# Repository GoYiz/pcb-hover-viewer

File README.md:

# PCB Hover Viewer

在线查看手机主板并进行“hover 关系高亮”的 Web 应用。

## 技术栈
- Next.js（App Router）
- TypeScript
- SQLite3 + Prisma
- Zustand
- （可选）PixiJS

## 核心能力（当前实现）
- 板卡列表/元信息 API
- 元件与走线几何 API
- 关系查询 API（component -> direct/net/trace）
- 板卡查看页 `/board/[id]`
- **互联网默认示例页 `/examples`（Python 抓取并预处理）**
- Hover 元件联动高亮：
  - 目标元件高亮
  - 直接关联元件高亮
  - 关联 Trace 高亮
- 关系侧边栏信息展示

## 快速开始
```bash
npm install
npm run db:generate
npm run db:push
npm run db:seed
npm run dev
```

打开：`http://localhost:3000/board/iphone-mainboard-demo`

## 目录结构
```text
app/
  api/boards/...        # API 路由
  board/[id]/page.tsx   # 查看器页面
components/
  BoardViewerClient.tsx
  PcbCanvas.tsx
lib/
  prisma.ts
  api.ts
prisma/
  schema.prisma
  seed.ts
store/
  viewerStore.ts
types/
  pcb.ts
```

## 架构文档
- `docs/ARCHITECTURE.md`

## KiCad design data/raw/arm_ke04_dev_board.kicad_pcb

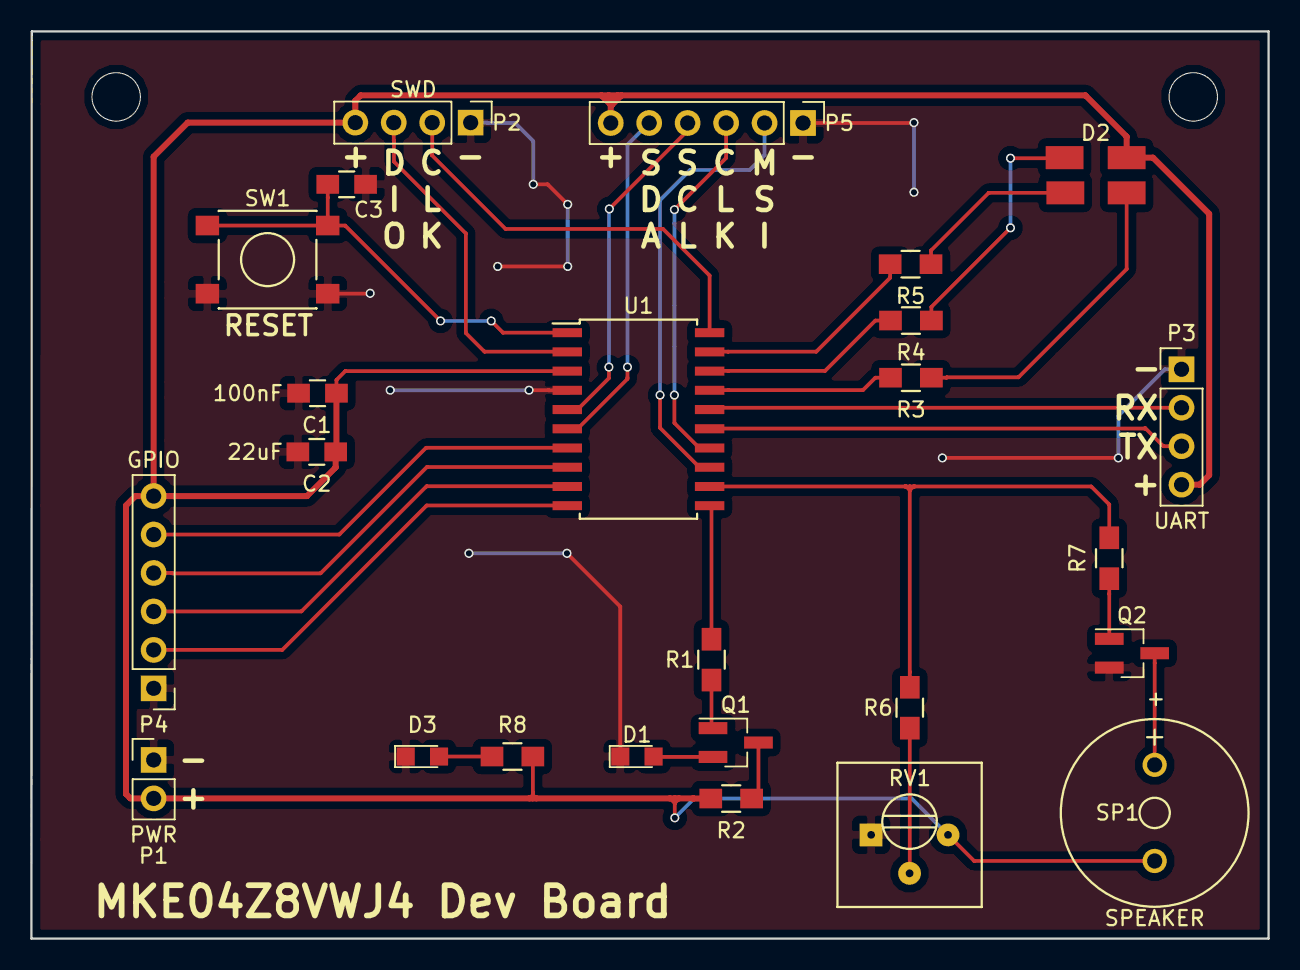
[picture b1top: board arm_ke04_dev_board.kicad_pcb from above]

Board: 2 copper layers, 81.7 x 59.9 mm, 25 parts (0 on the bottom side), 30 nets.

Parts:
C1, C3: 100nF; C_0805_HandSoldering
C2: 22uF; C_0805_HandSoldering
D1, D3: LED; LED_0805
D2: Led_RGB_CA; 4PLED+
P1: PWR; Pin_Header_Straight_1x02_Pitch2.54mm
P2: SWD; Pin_Header_Straight_1x04_Pitch2.54mm
P3: UART; Pin_Header_Straight_1x04_Pitch2.54mm
P4: GPIO; Pin_Header_Straight_1x06_Pitch2.54mm
P5: SPECIAL; Pin_Header_Straight_1x06_Pitch2.54mm
Q1: Q_NPN_BCE; SOT-23_Handsoldering
Q2: Q_NMOS_GSD; SOT-23_Handsoldering
R1: 10K; R_0805_HandSoldering
R2: 500R; R_0805_HandSoldering
R3, R4, R5, R8: 1K; R_0805_HandSoldering
R6, R7: 0R; R_0805_HandSoldering
RV1: POT; Potentiometer_Trimmer-Suntan-TSR-3386P
SP1: SPEAKER; MagneticBuzzer_ProSignal_ABT-410-RC
SW1: SW_PUSH_SMALL; SW_SPST_PTS645
U1: MKE04Z8VWJ4; SOIC-20W_7.5x12.8mm_Pitch1.27mm

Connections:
/I2C_SCL: P5.4, U1.5
/I2C_SDA: P5.5, U1.6
/RESET: C3.1, SW1.1, U1.1
/SPI_CLK: P5.3, U1.14
/SPI_MOSI: P5.2, U1.13
/SWD_CLK: P2.2, U1.20
/SWD_DIO: P2.3, U1.2
/UART_RX: P3.2, U1.16
/UART_TX: P3.3, U1.15
GND: C1.2, C2.2, C3.2, D1.1, D3.1, P1.1, P2.1, P3.1, P4.1, P5.1, Q2.2, RV1.1, SW1.2, U1.4
unnamed: D1.2, Q1.2
unnamed: D2.2, R3.1
unnamed: D2.3, R4.1
unnamed: D2.4, R5.1
unnamed: D3.2, R8.1
unnamed: P4.2, U1.10
unnamed: P4.3, U1.9
unnamed: P4.4, U1.8
unnamed: P4.5, U1.7
unnamed: Q1.1, R1.1
unnamed: Q1.3, R2.1
unnamed: Q2.1, R7.1
unnamed: Q2.3, SP1.2
unnamed: R1.2, U1.11
unnamed: R3.2, U1.17
unnamed: R4.2, U1.18
unnamed: R5.2, U1.19
unnamed: R6.1, RV1.2
unnamed: R6.2, R7.2, U1.12
VDD: C1.1, C2.1, D2.1, P1.2, P2.4, P3.4, P4.6, P5.6, R2.2, R8.2, RV1.3, SP1.1, U1.3

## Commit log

2026-04-07 docs: add architecture design for pcb hover viewer
2026-04-07 docs: switch architecture to nextjs + sqlite with optional python pipeline
2026-04-07 feat: implement nextjs sqlite pcb hover viewer mvp
2026-04-07 fix: align react version with next 15 peer deps
2026-04-07 build: run prisma generate before next build
2026-04-07 chore: upgrade next to 15.5.6 for security patch
2026-04-07 chore: upgrade next to 16.2.2
2026-04-07 feat: add internet-sourced default examples with python preprocessing
2026-04-07 fix: parse traces and enable hover reactions for both components and traces
2026-04-07 feat: add animated trace flow and target pulse effects
2026-04-07 feat: replace svg mvp renderer with pixijs high-performance canvas renderer
2026-04-07 feat: restore trace flow and add layered pixi rendering with partial redraw
2026-04-07 feat: add zoom pan lod and relation request throttling cache
2026-04-07 feat: add box zoom minimap and client-side zero-request relation index
2026-04-07 feat: add layer toggles and component search-focus with box zoom and minimap refinements
2026-04-07 fix: restore highlight effect and finalize layer toggle plus component search focus
2026-04-07 fix: make visibleLayers prop optional for backward compatibility
2026-04-07 feat: add unified 2d/3d view mode with threejs renderer and shared interaction state
2026-04-07 fix: add @types/three and update typedRoutes config
2026-04-07 feat: apply unified tscircuit-inspired workbench ui and shared 2d-3d visual language
2026-04-08 fix: restore full workbench ui implementation after style redesign
2026-04-12 fix: restore renamed board api helpers for workbench ui
2026-04-12 fix: accept legacy board props in workbench client component
2026-04-12 feat: add leafer 2d validation renderer alongside pixi and three
2026-04-12 feat: add zoom pan box-zoom and focus navigation to leafer validation renderer
2026-04-12 fix: guard leafer rect position and size values for type safety
2026-04-12 refactor: switch default 2d renderer from pixi to leafer globally
2026-04-12 fix: dynamically import leafer-based 2d canvas to avoid server prerender issues
2026-04-12 fix: disable ssr for leafer-dependent board and examples pages
2026-04-12 fix: restore standard page wrappers after invalid dynamic server component attempt
2026-04-12 fix: force dynamic rendering for leafer-dependent pages
2026-04-12 fix: serve demo board page from built-in data to isolate leafer runtime issue
2026-04-12 debug: replace leafer workbench canvas with minimal runtime probe
2026-04-12 fix: restore dynamic canvas imports in workbench after debug probe
2026-04-12 debug: switch leafer probe to official nextjs init pattern
2026-04-12 fix: relax leafer probe local typing to match runtime api
2026-04-12 feat: restore real pcb primitives rendering with official leafer init
2026-04-12 feat: restore hover and relation highlight in leafer renderer
2026-04-12 feat: restore zoom pan and box-zoom interactions in leafer renderer
2026-04-12 perf: cache leafer nodes and switch hover updates to partial redraw
2026-04-12 feat: add grid crosshair and layer hud to leafer workbench
2026-04-12 feat: add selection and box-select interactions to leafer workbench
2026-04-12 feat: add measurement tool and update leafer interaction tips
2026-04-12 feat: add measurement tool to leafer workbench
2026-04-12 feat: enhance measurement tool with preview esc clear and delta display
2026-04-12 feat: add point snapping to leafer measurement tool
2026-04-12 feat: add orthogonal constraint and snap highlight to measurement tool
2026-04-12 feat: persist multiple measurements in leafer workbench
2026-04-12 feat: add measurement list panel to leafer workbench
2026-04-12 feat: add selectable measurement rows and per-item delete
2026-04-12 feat: add clear copy and hover interactions to measurement panel
2026-04-12 feat: add append selection and append box select interactions
2026-04-12 feat: add subtract box select and selection status bar
2026-04-12 feat: add selected objects panel to leafer workbench
2026-04-12 feat: add center and zoom actions for selected objects
2026-04-12 feat: add projection guides to measurement tool
2026-04-12 feat: add copy all measurements action
2026-04-12 fix: repair copy all measurements newline handling
2026-04-12 feat: add top and side toolbars to leafer workbench
2026-04-12 feat: add keyboard help overlay to leafer workbench
2026-04-12 feat: add inspector panel to leafer workbench
2026-04-12 feat: persist viewer url state for camera selection and layers
2026-04-12 test: add canvas state bridge for url state verification
2026-04-12 test: add synthetic 4x4 stress board example for performance validation
2026-04-12 feat: enhance search with focus select and zoom actions
2026-04-12 feat: add export actions for workbench shot and text
2026-04-12 fix: derive export filenames from current path
2026-04-12 feat: add measurement csv and selection json exports
2026-04-12 feat: add selection filter modes for components and traces
2026-04-12 feat: add fine-grained detail visibility toggles in leafer view
2026-04-12 feat: add adaptive label density strategy for leafer view
2026-04-12 fix: type adaptive label visibility state explicitly
2026-04-12 feat: add major and minor adaptive grid rendering
2026-04-12 feat: make trace hit radius adaptive to width and zoom
2026-04-12 feat: enhance relation inspector summaries for hover and multi-select
2026-04-12 feat: enhance measurement snapping with segment projection and center priority
2026-04-12 fix: write selection to url when focusing search result
2026-04-12 feat: persist tool filter and detail visibility in viewer url
2026-04-12 fix: type url-restored tool and filter states explicitly
2026-04-13 test: expose selection filter in canvas state bridge
2026-04-13 feat: export unified workbench session json
2026-04-13 feat: redesign pcb viewer with industrial console aesthetic
2026-04-13 feat: polish console ui with summary rail and richer inspector hierarchy
2026-04-13 feat: surface live canvas state in console summary rail
2026-04-13 feat: polish examples catalog with summary rail and dossier layout
2026-04-14 style: refine typography and spacing across console ui
2026-04-14 style: add restrained motion polish to console surfaces
2026-04-14 test: expose last export action in canvas state bridge
2026-04-14 test: add dom trigger for session export verification
2026-04-14 chore: remove temporary session export dom trigger
2026-04-14 fix: repair bridge text parsing for live summary rail
2026-04-14 feat: share selection and focus state across 2d and 3d views
2026-04-14 fix: pass shared selection props only to 3d canvas
2026-04-14 feat: extend shared 2d 3d state with view mode and clear selection
2026-04-14 feat: preserve relation target semantics from shared selection
2026-04-16 feat: add first-pass IPC-2581 importer and sample fixture
2026-04-16 feat: add first-pass ODB++ importer and sample fixture
2026-04-16 feat: improve importer bbox and net binding heuristics
2026-04-16 feat: expand importer geometry coverage for ipc and odb
2026-04-16 feat: improve ipc geometry extraction from layer features
2026-04-16 feat: complete ipc geometry importer with profile and hole support
2026-04-16 feat: harden ipc importer for production use
2026-04-16 feat: surface import telemetry in viewer ui
2026-04-16 feat: ship ipc import metadata artifacts
2026-04-16 fix: correct ipc component placement and net extraction
2026-04-16 feat: add ipc semantic trace classification
2026-04-16 docs: record ipc semantic alignment baseline
2026-04-17 feat: refine ipc geometry buckets and telemetry
2026-04-17 fix: remove duplicate geometry bucket declaration
2026-04-17 fix: sync import metadata geometry count types
2026-04-17 refactor: declutter ipc telemetry panels
2026-04-17 feat: render ipc pads and keepouts in 2d viewer
2026-04-17 feat: render ipc silkscreen overlay in 2d viewer
2026-04-17 feat: render ipc drill overlay in 2d viewer
2026-04-17 feat: add 2d overlay visibility controls
2026-04-17 feat: render ipc zones in 2d viewer
2026-04-17 feat: render ipc vias in 2d viewer
2026-04-17 refactor: organize 2d overlay controls
2026-04-17 feat: sync live overlay visibility into examples panel
2026-04-17 feat: add overlay visibility presets
2026-04-17 feat: highlight active overlay presets
2026-04-17 feat: bring overlay system into main board viewer
2026-04-17 refactor: surface live overlays in main board viewer
2026-04-17 feat: extend board geometry api contract for overlays
2026-04-17 feat: split board overlays into dedicated geometry model
2026-04-17 fix: add demo fallbacks for hosted board APIs
2026-04-17 feat: unify hosted board fallbacks for examples
2026-04-17 feat: render non-copper overlay geometry buckets
2026-04-18 feat: polish viewer overlay families and initial buckets
2026-04-18 feat: add viewer overlay family controls
2026-04-18 feat: sync overlay telemetry and add legends
2026-04-18 fix: refresh canvas bridge after overlay preset sync
2026-04-18 feat: align three viewer with overlay families
2026-04-18 feat: add three viewer state bridge and overlay materials
2026-04-18 feat: polish three viewer legend and overlay materials
2026-04-18 feat: add overlay inspect support for three viewer
2026-04-18 feat: add overlay inspect and family bucket summaries
2026-04-18 fix: restore three overlay hover registration
2026-04-18 feat: add accessible overlay inspect targets
2026-04-18 feat: add qa panel and example overlay targets
2026-04-18 feat: add viewer debug regression coverage
2026-04-18 feat: add inspect-aware viewer debug smoke tests
2026-04-18 feat: align overlay kinds with ipc2581 converter semantics
2026-04-18 feat: add db import chain and external bucket projection
2026-04-18 feat: productize board import and tighten ipc projection
2026-04-18 feat: narrow switch graphics projection gap
2026-04-18 docs: finalize ipc graphics parity closeout
2026-04-18 feat: deepen overlay relation interactions
2026-04-18 feat: enrich overlay highlight and export state
2026-04-18 feat: deepen overlay selection workflows
2026-04-19 feat: enrich overlay semantic exports
2026-04-19 feat: deepen overlay relation summaries
2026-04-19 feat: unionize selection relation graph
2026-04-19 fix: unify overlay inspect initialization
2026-04-19 fix: suppress unbound overlay relation fanout
2026-04-19 feat: enrich structure overlay relations
2026-04-19 feat: add weak document overlay relations
2026-04-19 feat: add weak fabrication overlay relations
2026-04-19 feat: add weak pad package relations
2026-04-19 fix: allow pad stack local relations
2026-04-19 feat: annotate relation monitor semantics
2026-04-19 feat: apply relation class visual tones
2026-04-19 feat: color related components and traces by relation class
2026-04-19 feat: include relation semantics in exports
2026-04-19 feat: add export automation controls
2026-04-19 feat: enrich export relation metadata
2026-04-19 docs: add overlay relations delivery closeout
2026-04-19 feat: align odbpp import with viewer geometry model
2026-04-19 test: add odb db import chain validation
2026-04-19 feat: add odb electrical net inference
2026-04-19 test: codify odb semantic coverage bounds
2026-04-19 docs: add odbpp import status summary
2026-05-10 docs: add project handoff
